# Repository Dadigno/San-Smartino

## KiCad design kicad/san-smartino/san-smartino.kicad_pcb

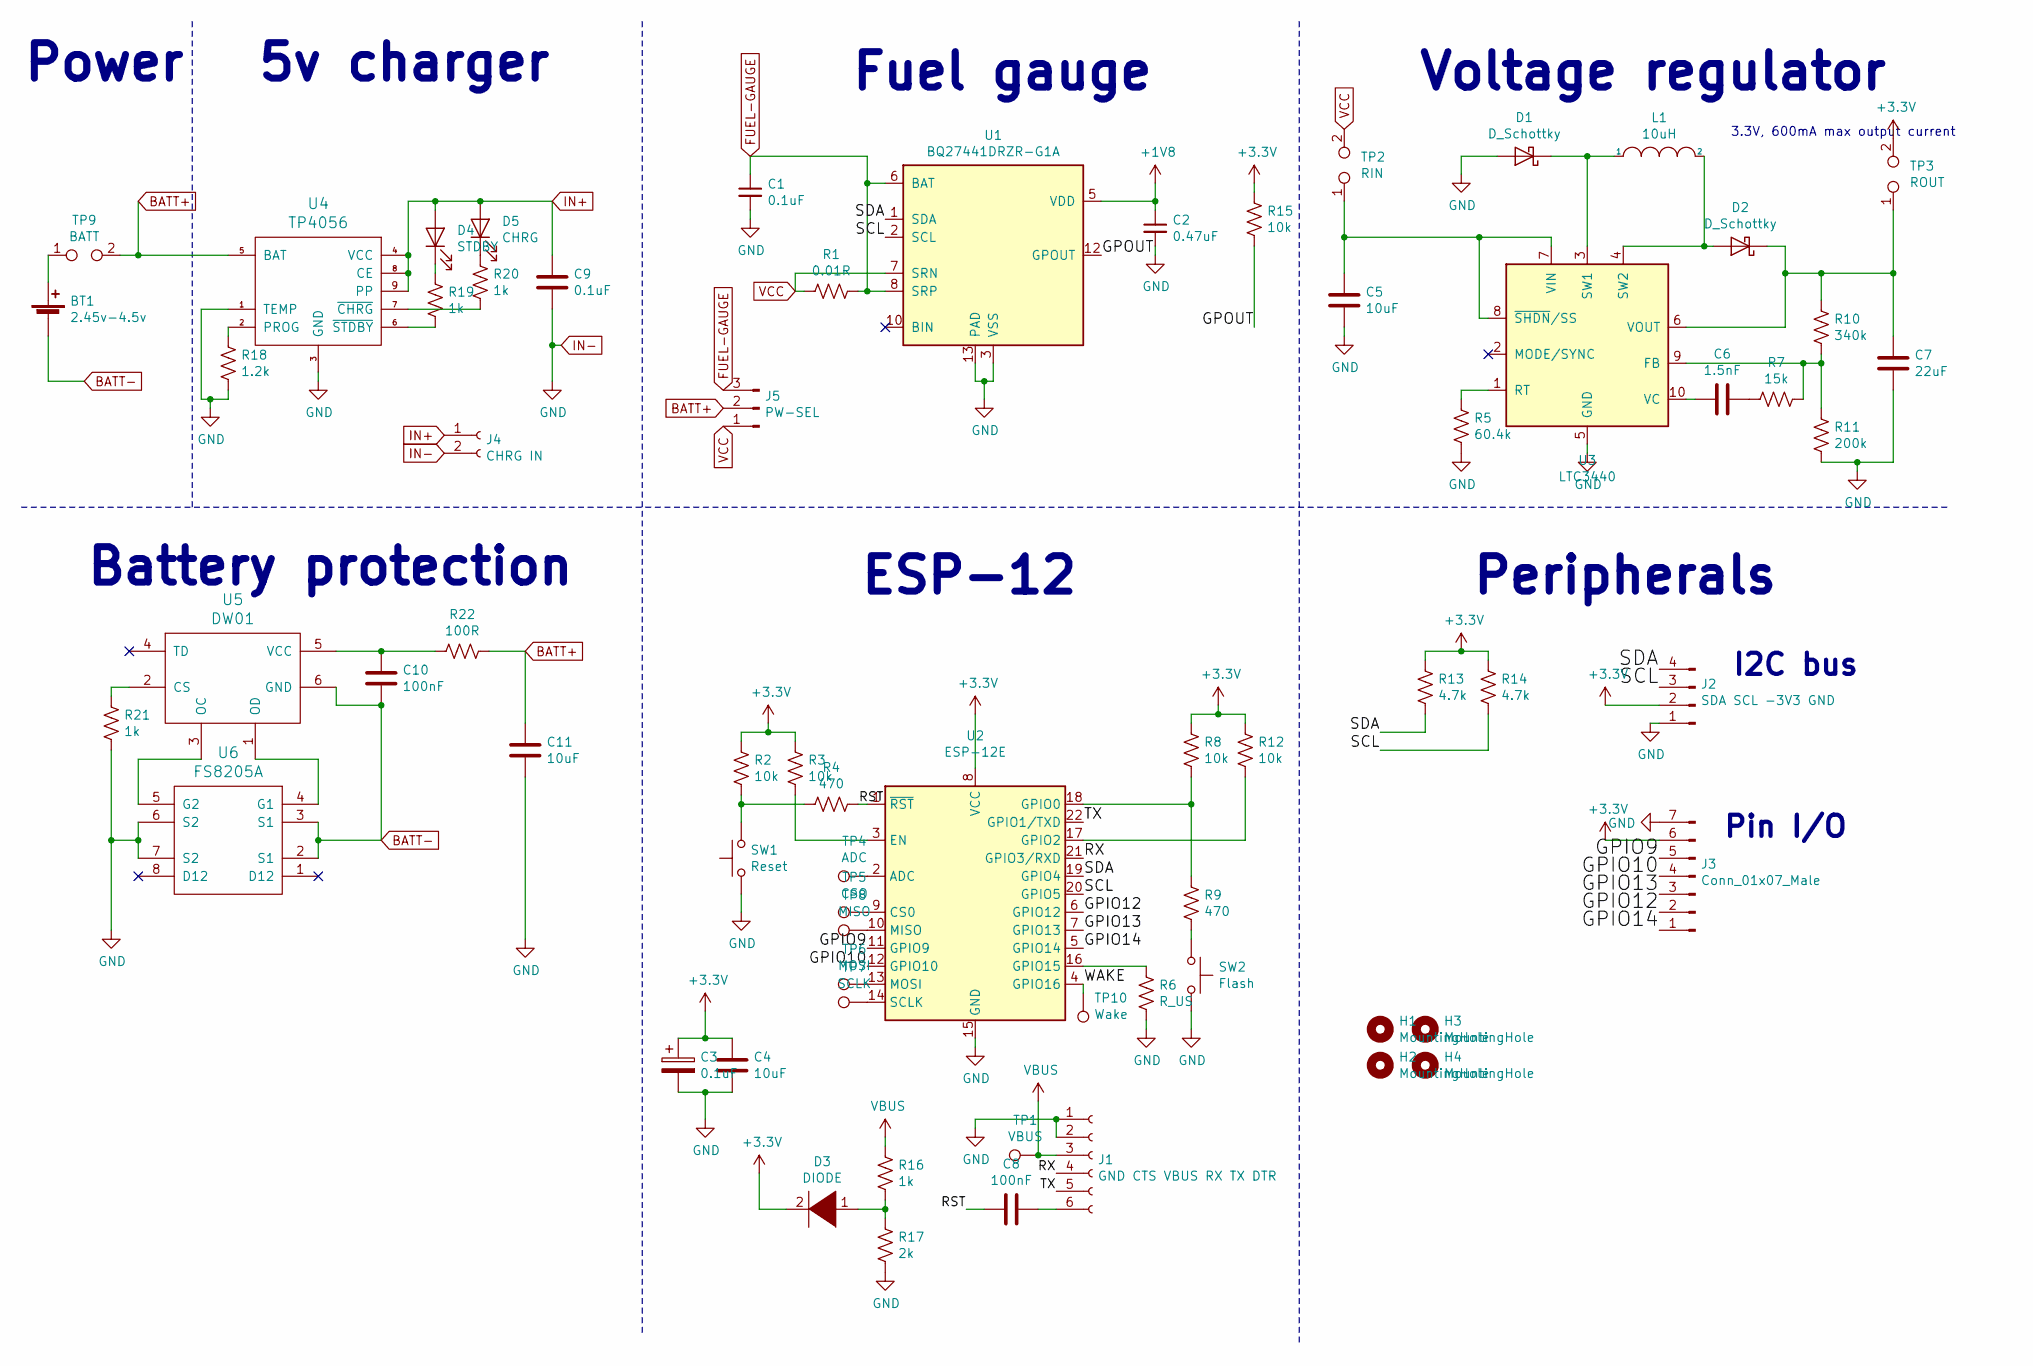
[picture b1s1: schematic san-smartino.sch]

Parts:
BT1: 2.45v-4.5v; 18650-battery-metal-clips
C1, C9: 0.1uF; C_0805_2012Metric_Pad1.15x1.40mm_HandSolder
C2: 0.47uF; C_0805_2012Metric_Pad1.15x1.40mm_HandSolder
C3: 0.1uF; C_1206_3216Metric_Pad1.42x1.75mm_HandSolder
C4: 10uF; CP_EIA-6032-15_Kemet-U_Pad2.25x2.35mm_HandSolder
C5, C11: 10uF; C_0805_2012Metric_Pad1.15x1.40mm_HandSolder
C6: 1.5nF; C_0805_2012Metric_Pad1.15x1.40mm_HandSolder
C7: 22uF; C_0805_2012Metric_Pad1.15x1.40mm_HandSolder
C8, C10: 100nF; C_0805_2012Metric_Pad1.15x1.40mm_HandSolder
D1, D2: D_Schottky; D_SOD-323_HandSoldering
D3: DIODE; D_SMA
D4: STDBY; LED_0603_1608Metric_Pad1.05x0.95mm_HandSolder
D5: CHRG; LED_0603_1608Metric_Pad1.05x0.95mm_HandSolder
H1, H2, H3, H4: MountingHole; MountingHole_3.2mm_M3_Pad_Via
J1: GND CTS VBUS RX TX DTR; PinHeader_1x06_P2.54mm_Vertical
J2: SDA SCL -3V3 GND; PinHeader_1x04_P2.54mm_Vertical
J3: Conn_01x07_Male; PinHeader_1x07_P2.54mm_Vertical
J4: CHRG IN; PinHeader_1x02_P2.54mm_Vertical
J5: PW-SEL; PinHeader_1x03_P2.54mm_Vertical
L1: 10uH; L_Taiyo-Yuden_NR-30xx_HandSoldering
R1: 0.01R; R_2512_6332Metric_Pad1.52x3.35mm_HandSolder
R2, R3, R8, R12, R15: 10k; R_0805_2012Metric_Pad1.15x1.40mm_HandSolder
R4, R9: 470; R_0805_2012Metric_Pad1.15x1.40mm_HandSolder
R5: 60.4k; R_0805_2012Metric_Pad1.15x1.40mm_HandSolder
R6: R_US; R_0805_2012Metric_Pad1.15x1.40mm_HandSolder
R7: 15k; R_0805_2012Metric_Pad1.15x1.40mm_HandSolder
R10: 340k; R_0805_2012Metric_Pad1.15x1.40mm_HandSolder
R11: 200k; R_0805_2012Metric_Pad1.15x1.40mm_HandSolder
R13, R14: 4.7k; R_0805_2012Metric_Pad1.15x1.40mm_HandSolder
R16, R19, R20, R21: 1k; R_0805_2012Metric_Pad1.15x1.40mm_HandSolder
R17: 2k; R_0805_2012Metric_Pad1.15x1.40mm_HandSolder
R18: 1.2k; R_0805_2012Metric_Pad1.15x1.40mm_HandSolder
R22: 100R; R_0805_2012Metric_Pad1.15x1.40mm_HandSolder
SW1: Reset; SW_SPST_EVQP0
SW2: Flash; PinHeader_1x02_P2.54mm_Vertical
TP1: VBUS; TestPoint_Pad_D1.5mm
TP2: RIN; TestPoint_2Pads_Pitch2.54mm_Drill0.8mm
TP3: ROUT; TestPoint_2Pads_Pitch2.54mm_Drill0.8mm
TP4: ADC; TestPoint_Pad_D1.5mm
TP5: CSO; TestPoint_Pad_D1.5mm
TP6: MOSI; TestPoint_Pad_D1.5mm
TP7: SCLK; TestPoint_Pad_D1.5mm
TP8: MISO; TestPoint_Pad_D1.5mm
TP9: BATT; TestPoint_2Pads_Pitch2.54mm_Drill0.8mm
TP10: Wake; TestPoint_Pad_D1.5mm
U1: BQ27441DRZR-G1A; Texas_S-PDSO-N12
U2: ESP-12E
U3: LTC3440; MSOP-10_3x3mm_P0.5mm
U4: TP4056; SOP-8-1EP_4.57x4.57mm_P1.27mm_EP4.57x4.45mm
U5: DW01; SOT-23-6_Handsoldering
U6: FS8205A; TSSOP-8_4.4x3mm_P0.65mm

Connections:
+1V8: C2.1, U1.5 (VDD)
+3V3: C3.1, C4.1, D3.2 (A), J2.2, J3.6, R2.1, R3.1, R8.1, R12.1, R13.1, R14.1, R15.1, TP3.2, U2.8 (VCC)
/GPIO9: J3.5, U2.11 (GPIO9)
/GPIO10: J3.4, U2.12 (GPIO10)
/GPIO12: J3.2, U2.6 (GPIO12)
/GPIO13: J3.3, U2.7 (GPIO13)
/GPIO14: J3.1, U2.5 (GPIO14)
/GPOUT: R15.2, U1.12 (GPOUT)
/RST: C8.2, R4.1, U2.1 (~RST)
/RX: J1.4, U2.21 (GPIO3/RXD)
/SCL: J2.3, R14.2, U1.2 (SCL), U2.20 (GPIO5)
/SDA: J2.4, R13.2, U1.1 (SDA), U2.19 (GPIO4)
/TX: J1.5, U2.22 (GPIO1/TXD)
/WAKE: TP10.1, U2.4 (GPIO16)
BATT+: C11.1, J5.2, R22.1, TP9.2, U4.5 (BAT)
BATT-: BT1.2 (-), C10.2, U5.6 (GND), U6.2 (S1), U6.3 (S1)
FUEL-GAUGE: C1.1, J5.3, R1.1, U1.6 (BAT), U1.8 (SRP)
IN+: C9.1, D4.2 (A), D5.2 (A), J4.1, U4.4 (VCC), U4.8 (CE), U4.9 (PP)
IN-: C1.2, C2.2, C3.2, C4.2, C5.2, C7.2, C9.2, C11.2, D1.2 (A), J1.1, J1.2, J2.1, J3.7, J4.2, R5.2, R6.2, R11.2, R17.2, R18.2, R21.2, SW1.1, SW2.2, U1.3 (VSS), U1.13 (PAD), U2.15 (GND), U3.5 (GND), U4.1 (TEMP), U4.3 (GND), U6.6 (S2), U6.7 (S2)
unnamed: BT1.1 (+), TP9.1
unnamed: C5.1, TP2.1, U3.7 (VIN), U3.8 (~SHDN~/SS)
unnamed: C6.1, R7.2
unnamed: C6.2, U3.10 (VC)
unnamed: C7.1, D2.1 (K), R10.1, TP3.1, U3.6 (VOUT)
unnamed: C8.1, J1.6
unnamed: C10.1, R22.2, U5.5 (VCC)
unnamed: D1.1 (K), L1.1, U3.3 (SW1)
unnamed: D2.2 (A), L1.2, U3.4 (SW2)
unnamed: D3.1 (K), R16.2, R17.1
unnamed: D4.1 (K), R19.1
unnamed: D5.1 (K), R20.1
unnamed: R2.2, R4.2, SW1.2
unnamed: R3.2, U2.3 (EN)
unnamed: R5.1, U3.1 (RT)
unnamed: R6.1, U2.16 (GPIO15)
unnamed: R8.2, R9.1, U2.18 (GPIO0)
unnamed: R9.2, SW2.1
unnamed: R7.1, R10.2, R11.1, U3.9 (FB)
unnamed: R12.2, U2.17 (GPIO2)
unnamed: R18.1, U4.2 (PROG)
unnamed: R19.2, U4.6 (~STDBY)
unnamed: R20.2, U4.7 (~CHRG)
unnamed: R21.1, U5.2 (CS)
unnamed: TP4.1, U2.2 (ADC)
unnamed: TP5.1, U2.9 (CS0)
unnamed: TP6.1, U2.13 (MOSI)
unnamed: TP7.1, U2.14 (SCLK)
unnamed: TP8.1, U2.10 (MISO)
unnamed: U5.1 (OD), U6.4 (G1)
unnamed: U5.3 (OC), U6.5 (G2)
VBUS: J1.3, R16.1, TP1.1
VCC: J5.1, R1.2, TP2.2, U1.7 (SRN)

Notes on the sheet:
Power
Fuel gauge
ESP-12
3.3V, 600mA max output current
Voltage regulator
Peripherals
I2C bus
Pin I/O
5v charger
Battery protection

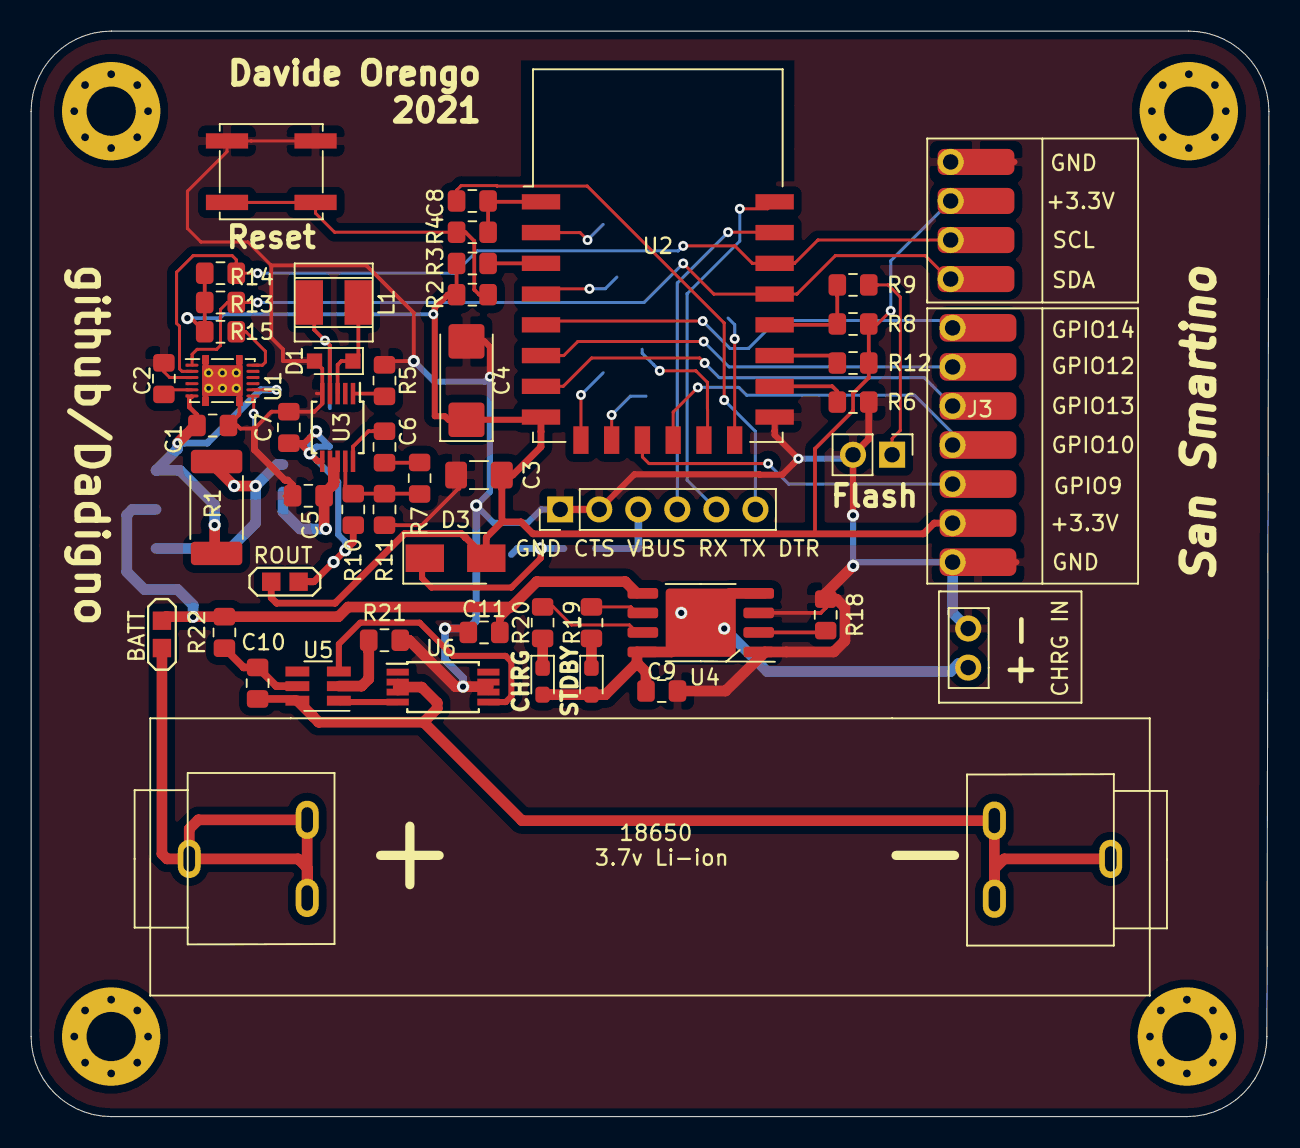
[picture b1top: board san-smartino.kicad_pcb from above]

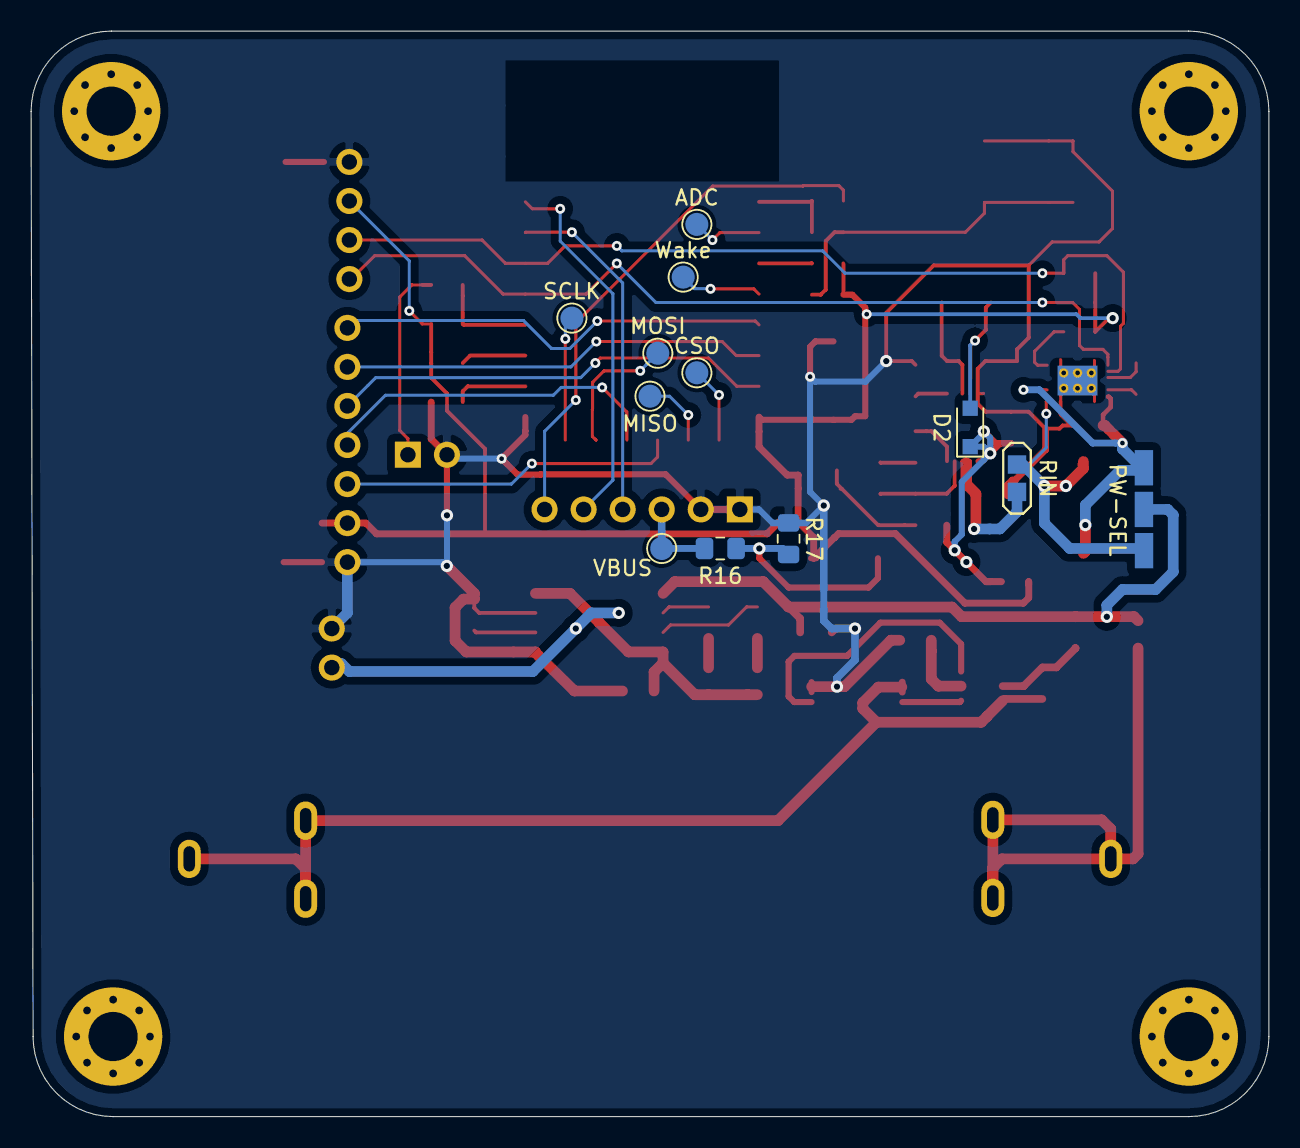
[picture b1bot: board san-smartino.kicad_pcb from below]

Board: 2 copper layers, 80.5 x 70.6 mm, 67 parts (12 on the bottom side), 52 nets.

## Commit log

2021-03-09 flow-chart
2021-03-12 useless file
2021-03-12 datasheets
2021-03-12 kicad project
2021-03-12 media
2021-03-12 tiny updated
2021-03-20 media updated
2021-03-20 3d model library added
2021-03-20 schematic updated, second battery and edgecut
2021-03-30 updated board
2021-03-30 new datasheet for circuit protection
2021-03-30 added missed 3d models
2021-03-30 deleted
